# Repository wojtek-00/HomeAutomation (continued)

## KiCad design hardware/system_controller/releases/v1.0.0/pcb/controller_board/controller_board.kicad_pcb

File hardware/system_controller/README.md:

# ESP32 Modular DIN Rail Controller for ESPHome

This repository contains PCB schematics and PCB design files for a modular ESP32-based controller designed for use with ESPHome.

The controller supports expansion modules that provide additional functionality such as extra GPIO, PWM outputs, relays, and other peripherals.

---

## Features

- ESP32-based controller
- Designed for ESPHome
- Modular expansion system
- DIN rail mount enclosure
- Easy integration with custom modules

---

## Supported Expansion Modules

Examples of supported modules:

- GPIO expanders
- PWM output modules
- Relay modules
- Analog input modules
- Custom extension boards

---

## Enclosure Parameters (Fusion 360)

| Parameter | Value |
|---|---|
| Enclosure type | `RailEnclosure_One_Side` |
| Board width | `45 mm` |

---

## Project Structure

```text
/pcb            -> PCB design files
/schematics     -> Electrical schematics
/fusion360      -> Enclosure and mechanical design
/docs           -> Documentation
```

---

## Software

The controller is designed to work with ESPHome firmware.

ESPHome allows easy integration with Home Assistant and other home automation systems.

More information:
https://esphome.io/

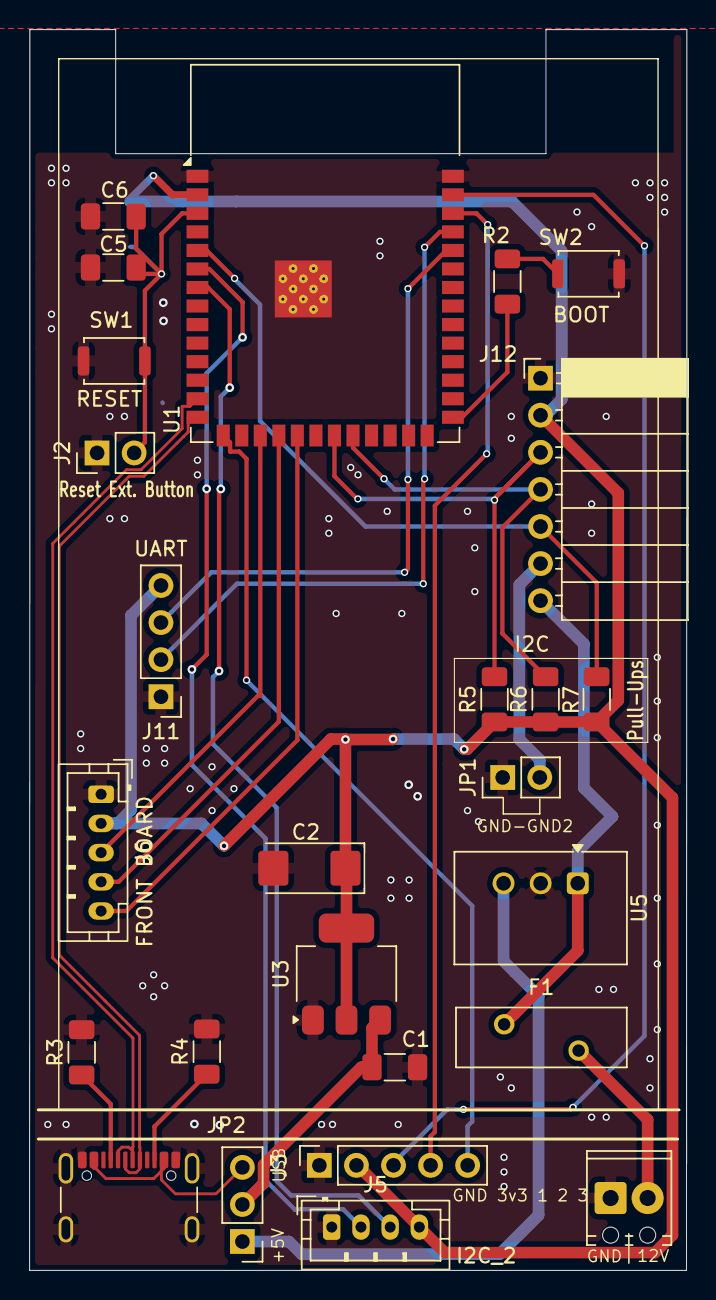
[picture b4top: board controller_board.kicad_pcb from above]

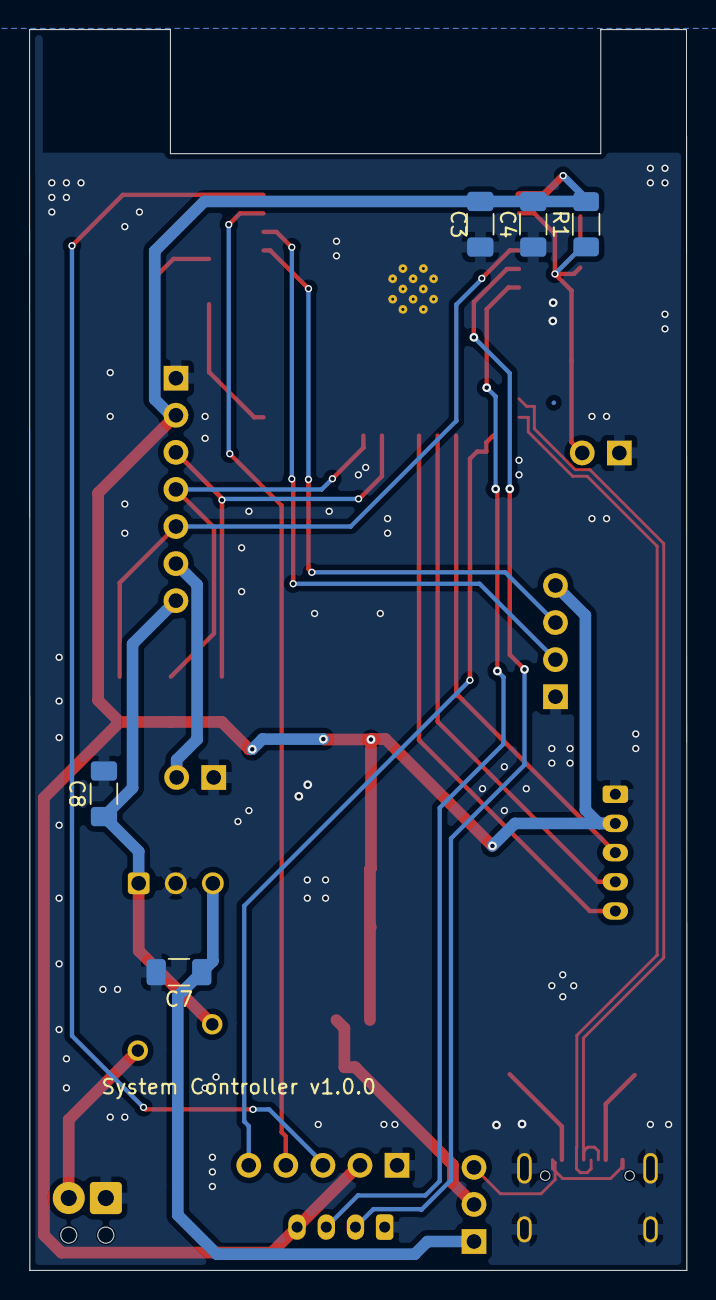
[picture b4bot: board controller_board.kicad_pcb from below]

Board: 2 copper layers, 45.0 x 85.0 mm, 31 parts (5 on the bottom side), 28 nets.

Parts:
C1: 10uF; C_1206_3216Metric_Pad1.33x1.80mm_HandSolder
C2: 22uF; CP_EIA-6032-15_Kemet-U
C3, C7, C8: 22uF; C_1206_3216Metric_Pad1.33x1.80mm_HandSolder
C4, C6: 100nF; C_1206_3216Metric_Pad1.33x1.80mm_HandSolder
C5: 1uF; C_1206_3216Metric_Pad1.33x1.80mm_HandSolder
F1: 1,1A, PTC; Fuse_BelFuse_0ZRE0033FF_L11.4mm_W3.8mm
J1: USB_C_Receptacle_USB2.0_16P; USB_C_Receptacle_GCT_USB4105-xx-A_16P_TopMnt_Horizontal
J2: Conn_01x02_Pin; PinHeader_1x02_P2.54mm_Vertical
J3: Conn_01x05_Socket; PinSocket_1x05_P2.54mm_Vertical
J4: Screw_Terminal_01x02; TerminalBlock_Phoenix_MPT-0,5-2-2.54_1x02_P2.54mm_Horizontal
J5: Conn_01x04_Pin; JST_PH_B4B-PH-K_1x04_P2.00mm_Vertical
J6: Conn_01x05_Socket; JST_PH_B5B-PH-K_1x05_P2.00mm_Vertical
J11: Conn_01x04_Pin; PinHeader_1x04_P2.54mm_Vertical
J12: Conn_01x07_Pin; PinSocket_1x07_P2.54mm_Horizontal_Right
JP1: Jumper_2_Bridged; PinHeader_1x02_P2.54mm_Vertical
JP2: Jumper_3_Open; PinHeader_1x03_P2.54mm_Vertical
R1, R5, R6, R7: 10k; R_1206_3216Metric_Pad1.30x1.75mm_HandSolder
R2: 100; R_1206_3216Metric_Pad1.30x1.75mm_HandSolder
R3, R4: 5.1k; R_1206_3216Metric_Pad1.30x1.75mm_HandSolder
SW1: RESET; SW_Push_SPST_NO_Alps_SKRK
SW2: BOOT; SW_Push_SPST_NO_Alps_SKRK
U1: ESP32-S3-WROOM-1
U3: AMS1117-3.3; SOT-223-3_TabPin2
U5: TSR1-2450E; Converter_DCDC_TRACO_TSR1-xxxxE_THT

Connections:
+3V3: C2.1, C3.1, C4.1, J3.2, J5.4, J6.2, J11.4, J12.2, R1.1, R5.1, R6.1, R7.1, U1.2 (3V3), U3.2 (VO)
+5V_USB: J1.A4 (VBUS), J1.A9 (VBUS), J1.B4 (VBUS), J1.B9 (VBUS), JP2.3 (B)
+12V: C8.1, F1.1, J12.7, U5.1 (Vin)
/LED_B: J6.5, U1.19 (IO11)
/LED_G: J6.4, U1.18 (IO10)
/LED_R: J6.3, U1.17 (IO9)
BOOT: R2.1, U1.27 (IO0)
D+: J1.A6 (D+), J1.B6 (D+), U1.14 (USB_D+)
D-: J1.A7 (D-), J1.B7 (D-), U1.13 (USB_D-)
EN: C5.1, C6.1, J2.2, R1.2, SW1.2, U1.3 (EN)
GND: C1.2, C2.2, C3.2, C4.2, C5.2, C6.2, C7.2, C8.2, J1.A1 (GND), J1.A12 (GND), J1.B1 (GND), J1.B12 (GND), J1.S1 (SHIELD), J2.1, J3.1, J4.1, J5.1, J6.1, J11.1, J12.1, JP1.1 (A), R3.2, R4.2, SW1.1, SW2.2, U1.1 (GND), U1.40 (GND), U1.41 (GND), U3.1 (GND), U5.2 (GND)
GND_2: J12.6, JP1.2 (B)
GPIO_1: J3.3, U1.39 (IO1)
GPIO_2: J3.4, U1.38 (IO2)
GPIO_3: J3.5, U1.15 (IO3)
I2C_SCL: J12.4, R6.2, U1.22 (IO14)
I2C_SCL_2: J5.3, U1.7 (IO7)
I2C_SDA: J12.3, R5.2, U1.21 (IO13)
I2C_SDA_2: J5.2, U1.6 (IO6)
INT: J12.5, R7.2, U1.5 (IO5)
unnamed: J1.A5 (CC1), R3.1
unnamed: J1.B5 (CC2), R4.1
unnamed: F1.2, J4.2
unnamed: C7.1, JP2.1 (A), U5.3 (Vout)
unnamed: C1.1, JP2.2 (C), U3.3 (VI)
unnamed: R2.2, SW2.1
RXD0: J11.3, U1.36 (RXD0)
TXD0: J11.2, U1.37 (TXD0)

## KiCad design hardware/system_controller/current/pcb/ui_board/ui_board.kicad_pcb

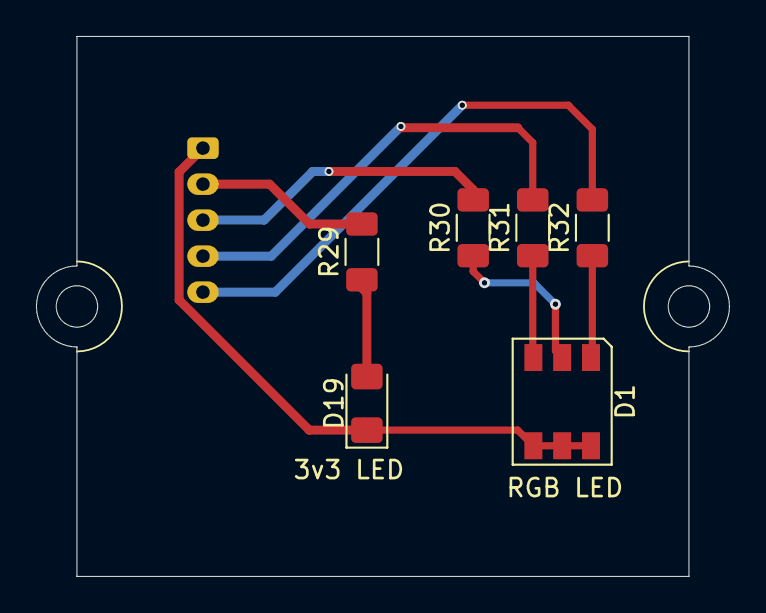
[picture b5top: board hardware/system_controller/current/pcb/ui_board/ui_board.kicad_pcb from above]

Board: 2 copper layers, 38.5 x 30.0 mm, 7 parts (1 on the bottom side), 9 nets.

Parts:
D1: LED_SMD_5050; LED_WS2812_PLCC6_5.0x5.0mm_P1.6mm
D19: 3v3 LED; LED_1206_3216Metric_Pad1.42x1.75mm_HandSolder
J6: Conn_01x05_Socket; JST_PH_B5B-PH-K_1x05_P2.00mm_Vertical
R29, R30, R31, R32: 330; R_1206_3216Metric_Pad1.30x1.75mm_HandSolder

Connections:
+3V3: J6.2, R29.2
/LED_B: J6.5, R32.2
/LED_G: J6.4, R31.2
/LED_R: J6.3, R30.2
GND: D1.4 (GND), D1.5 (GND), D1.6 (GND), D19.1 (K), J6.1
unnamed: D1.1 (BLUE), R32.1
unnamed: D1.3 (GREEN), R31.1
unnamed: D1.2 (RED), R30.1
unnamed: D19.2 (A), R29.1

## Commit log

2026-05-28 [ADD] first commit
2026-05-28 [ADD] README.md
2026-05-28 [ADD] tooling data
2026-05-28 [FIX] layout of template extention board
2026-05-31 [CHANGE] i2c adressing
2026-05-31 [ADD] two rows extention module
2026-05-31 [DELETE] some random dir
2026-05-31 [ADD] lauout for relay expander pcb
2026-05-31 [ADD] ui board template
2026-05-31 [ADD] ui-board for relay - basic layout
2026-06-01 [ADD] ui_board finished setup]
2026-06-01 [UPDATE] ui_board connector position
2026-06-01 [PDATE] ui module]
2026-06-01 [FIX] move connector on ui board
2026-06-01 [FIX] problem with connector to expander board
2026-06-01 [ADD] board connector
2026-06-01 [FIX] placement of connector for UI panel
2026-06-01 [ADD] generate step file for relay main controller
2026-06-02 [ADD] routing on main pcb board
2026-06-02 [FIX] add 12V trace for expanders and generate gerber for all relays related boards
2026-06-08 [ADD] firmware for sprinkler
2026-06-08 [ADD] path to git repo
2026-06-08 [ADD] data for pin in relay expander
2026-06-08 [FIX] 23xxx instead od 23017
2026-06-08 [ADD] sprinkler module
2026-06-08 [FIX] component name
2026-06-08 [FIX] mct name
2026-06-08 [ADD] 8 inputs and outputs for sprinkler extender
2026-06-08 [UPDATE] naming convention
2026-06-08 [FIX] add missing enable buttons for sprinkler extention board
2026-06-08 [ADD] device id
2026-06-08 [ADD] rename device_id
2026-06-08 [ADD] device id for switches
2026-06-08 [ADD] device id for time
2026-06-09 [ADD] relay_expander firmware
2026-06-16 [ADD] yaml configs for espHome
2026-06-17 [ADD] packages
2026-06-24 [UPDATE] firmware
2026-06-24 [ADD] logic for one relay gate
2026-06-24 [ADD] current operation for one relay gate controller
